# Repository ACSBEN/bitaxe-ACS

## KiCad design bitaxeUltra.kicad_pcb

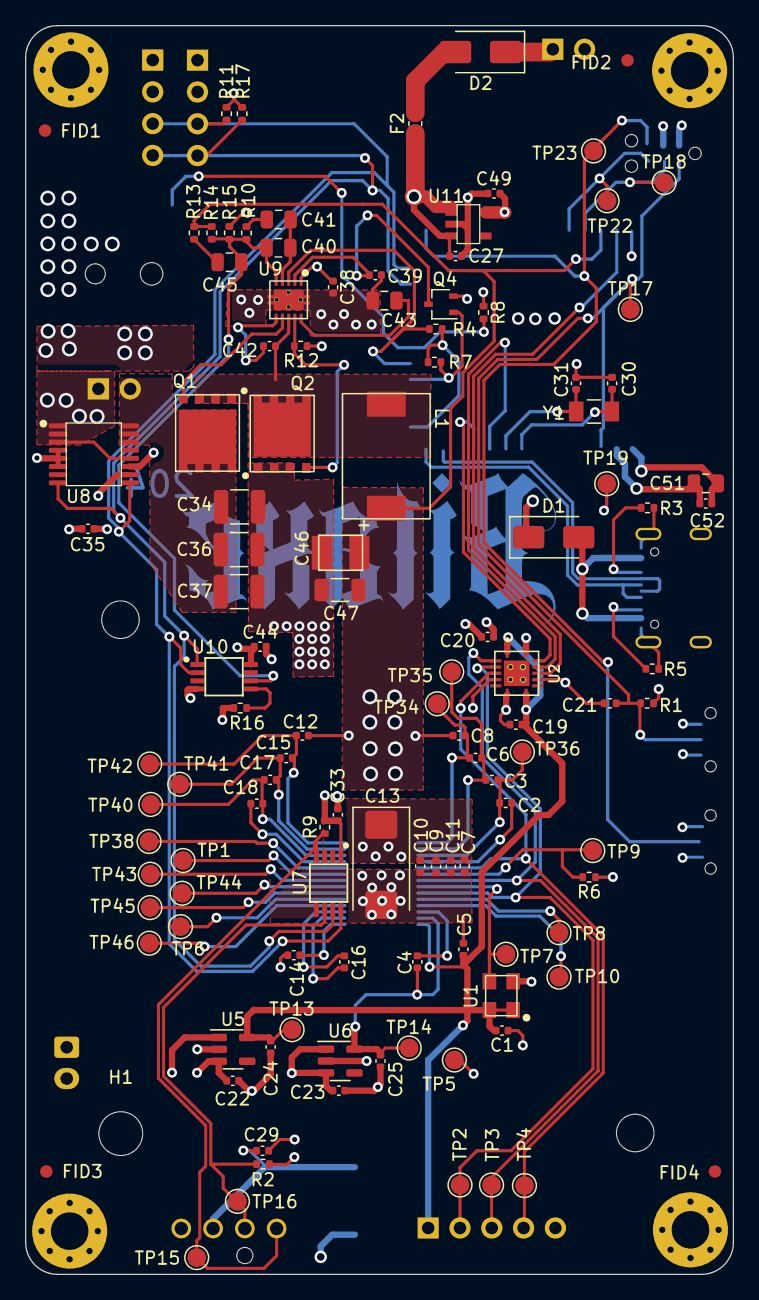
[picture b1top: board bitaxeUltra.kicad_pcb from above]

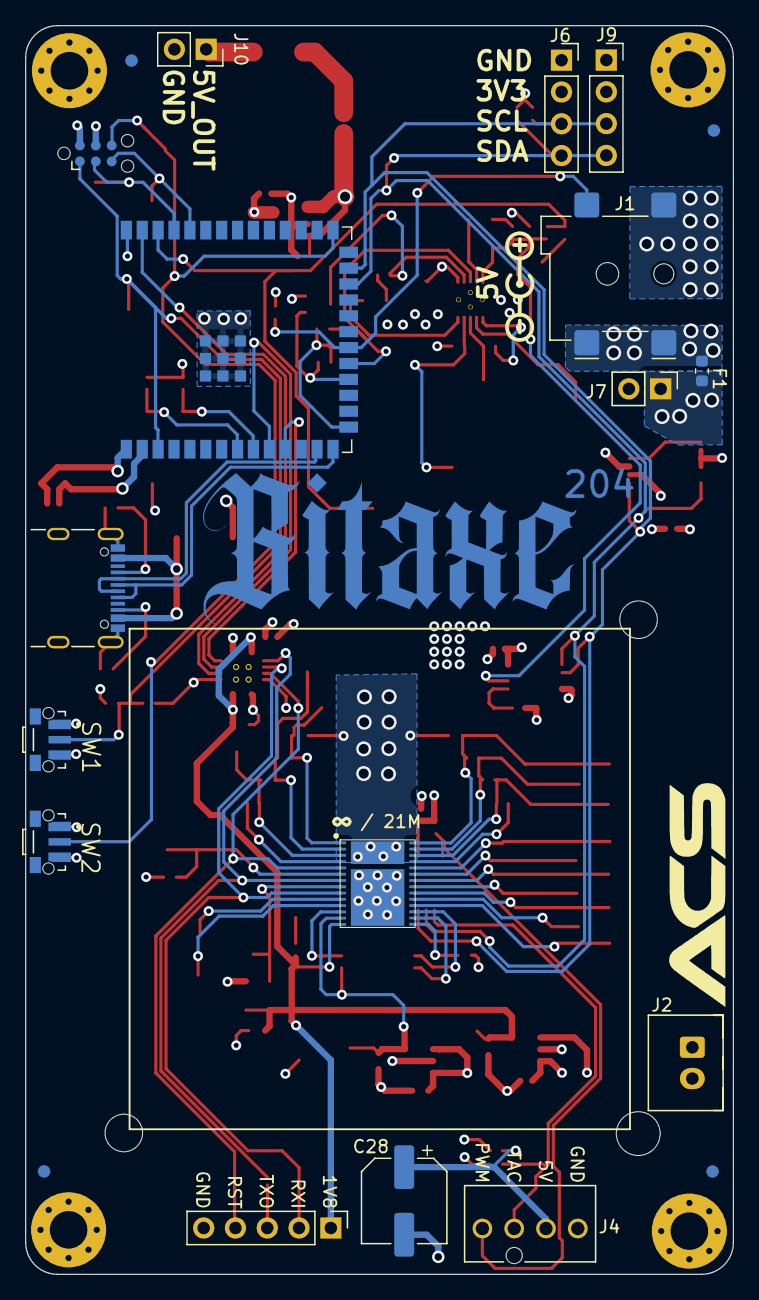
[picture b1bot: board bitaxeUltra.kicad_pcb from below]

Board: 4 copper layers, 56.5 x 99.8 mm, 143 parts (21 on the bottom side), 64 nets.

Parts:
C1, C7, C9, C19, C20, C29, C33, C42, C52: 0.1uF; C_0402_1005Metric
C2, C3, C4, C5, C6, C8, C10, C11, C12, C14, C15, C16, C17, C18, C21, C22, C23, C24, C25, C27, C35, C38, C44, C49: 1uF; C_0402_1005Metric
C13: 330uF; CP_EIA-7343-31_Kemet-D_Pad2.25x2.55mm_HandSolder
C28: 220uF; CP_Elec_6.3x7.7
C30, C31: 6.8pF; C_0402_1005Metric
C34, C36, C37: 47uF; C_1210_3225Metric
C39: 3.3nF; C_0402_1005Metric
C40: 180pF; C_0805_2012Metric
C41: 1.5nF; C_0805_2012Metric
C43, C51: 10uF; C_0805_2012Metric
C45: 470pF; C_0805_2012Metric
C46: 220uF; CAP_2R5TPE220MAFB
C47: 100uF; C_1206_3216Metric
D1, D2: SS310; D_SMA
F1: 5v 5a; Fuse_0603_1608Metric
F2: 5v 1A; Fuse_0603_1608Metric
FID1, FID2, FID3, FID4, FID5, FID6, FID7, FID8: Fiducial; Fiducial_1mm_Mask2mm
H1, H5, H6: MountingHole; MountingHole_3.5mm
H7, H8, H9, H10: MountingHole_Pad; MountingHole_3mm_Pad_Via
J1: 54-00164; BarrelJack_Wuerth_694106106102_2.0x5.5mm
J2: Conn_01x02; JST_XH_B2B-XH-A_1x02_P2.50mm_Vertical
J3: Conn_01x05; PinHeader_1x05_P2.54mm_Vertical
J4: Conn_01x04; 470531000
J5: TC2030-IDC; Tag-Connect_TC2030-IDC-NL_2x03_P1.27mm_Vertical
J6, J9: Conn_01x04; PinSocket_1x04_P2.54mm_Vertical
J7: Conn_01x02; PinHeader_1x02_P2.54mm_Vertical
J8: USB_C_Receptacle_USB2.0; USB_C_Receptacle_GCT_USB4105-xx-A_16P_TopMnt_Horizontal
J10: Conn_01x02; PinSocket_1x02_P2.54mm_Vertical
L1: 150nH; FP1005R1-R15-R
Q1, Q2: CSD17311Q5
Q4: 2N7002K; SOT-323_SC-70
R1, R4, R6, R7, R9: 10k; R_0402_1005Metric
R2: 5.6k; R_0402_1005Metric
R3, R5: 5.1k; R_0402_1005Metric
R8: 1M; R_0402_1005Metric
R10: 3.83k; R_0402_1005Metric
R11, R17: 4.7k; R_0402_1005Metric
R12: 4.12k; R_0402_1005Metric
R13: 1.33k; R_0402_1005Metric
R14: 4.99k; R_0402_1005Metric
R15: 3.32k; R_0402_1005Metric
R16: 80.6k; R_0402_1005Metric
SW1, SW2: GT-TC029B-H025-L1N; SW_TL3340AF160QG
TP1, TP2, TP3, TP4, TP5, TP6, TP7, TP8, TP9, TP10, TP13, TP14, TP15, TP16, TP17, TP18, TP19, TP22, TP23, TP34, TP35, TP36, TP38, TP40, TP41, TP42, TP43, TP44, TP45, TP46: TestPoint; TestPoint_Pad_D1.5mm
U1: 25MHz; O 25,0-JO32-B-1V3-1-T1-LF
U2: TXB0104RGYR; TXB0104
U3: polarity
U5: MCP1824T-1802E; SOT-23-5
U6: MCP1824T-0802E; SOT-23-5
U7: EMC2101; TSSOP-8_3x3mm_P0.65mm
U8: INA260; TSSOP-16_4.4x5mm_P0.65mm
U9: TPS40305
U10: DS4432U+; TSSOP-8_3x3mm_P0.65mm
U11: RT9080-33GJ5
U12: ESP32-S3-WROOM-1
U14: BM1366_mode1; BM1366
Y1: 32.768kHz; SC32S-7PF20PPM

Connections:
/3V3: C20.1, C33.1, C35.1, C44.1, C49.1, C51.1, C52.1, J5.2, J6.2, J9.2, R1.1, R2.2, R4.1, R7.1, R8.1, R9.2, R11.2, R17.2, TP19.1, U2.14 (VCCB), U7.1 (VDD), U8.10 (VS), U10.8 (VCC), U11.5 (VOUT), U12.2 (3V3), U12.15 (GPIO3/TOUCH3/ADC1_CH2*)
/5V: C22.1, C23.1, C27.1, C28.1, C29.1, C34.1, C36.1, C37.1, C38.1, D1.1, F2.1, J2.2, J4.2, J7.2, Q1.5 (D), U5.1 (VIN), U5.3 (EN), U6.1 (VIN), U6.3 (EN), U8.14 (IN-), U8.15 (IN-), U8.16 (IN-), U9.1 (VDD), U11.1 (VIN), U11.3 (EN)
/BM1366/0V8: C4.1, C25.1, TP14.1, U6.5 (VOUT), U14.13 (VDDIO_08_0)
/BM1366/1V8: C1.2, C5.1, C19.1, C24.1, J3.1, TP13.1, U1.1 (EN), U1.4 (VIN), U2.1 (VCCA), U2.8 (OE), U5.5 (VOUT), U14.14 (VDDIO_18_0)
/BM1366/ADDR0: TP8.1, U14.10 (ADDR0)
/BM1366/ADDR1: TP10.1, U14.11 (ADDR1)
/BM1366/BI: R6.2, TP9.1, U14.6 (BI)
/BM1366/BO: TP1.1, U14.23 (BO)
/BM1366/CI: J3.2, TP2.1, U2.3 (A2), U14.9 (CI)
/BM1366/CLKI: TP7.1, U1.3 (OUT), U14.8 (CLKI)
/BM1366/CLKO: TP44.1, U14.21 (CLKO)
/BM1366/CO: TP45.1, U14.20 (CO)
/BM1366/INV_CLKO: TP6.1, U14.19 (INV_CLKO)
/BM1366/NRSTO: TP38.1, U14.24 (NRSTO)
/BM1366/PIN_MODE: TP46.1, U14.18 (PIN_MODE)
/BM1366/RI: TP43.1, U14.22 (RI)
/BM1366/RO: J3.3, TP3.1, U2.2 (A1), U14.7 (RO)
/BM1366/RST_N: J3.4, TP4.1, U2.4 (A3), U14.5 (NRSTI)
/BM1366/VDD1_0: C6.2, C8.1, TP34.1, U14.1 (VDD1_0)
/BM1366/VDD1_1: C12.2, C15.1, TP42.1, U14.28 (VDD1_1)
/BM1366/VDD2_0: C3.2, C6.1, TP35.1, U14.2 (VDD2_0)
/BM1366/VDD2_1: C15.2, C17.1, TP41.1, U14.27 (VDD2_1)
/BM1366/VDD3_0: C2.2, C3.1, TP36.1, U14.3 (VDD3_0)
/BM1366/VDD3_1: C17.2, C18.1, TP40.1, U14.26 (VDD3_1)
/ESP32/5V_OUT: D2.1, J10.1
/ESP32/EN: C21.1, J5.1, R1.2, SW1.2, TP17.1, U12.3 (EN)
/ESP32/IO0: J5.6, SW2.2, TP23.1, U12.27 (GPIO0/BOOT*)
/ESP32/PWR_EN: Q4.1 (G), R7.2, U12.18 (GPIO10/TOUCH10/ADC1_CH9/FSPICS0/FSPIIO4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)
/ESP32/P_RX: J5.5, TP22.1, U12.36 (U0RXD/GPIO44/CLK_OUT2)
/ESP32/P_TX: J5.3, TP18.1, U12.37 (U0TXD/GPIO43/CLK_OUT1)
/ESP32/XIN32: C30.1, U12.8 (GPIO15/U0RTS/ADC2_CH4/XTAL_32K_P), Y1.1
/ESP32/XOUT32: C31.1, U12.9 (GPIO16/U0CTS/ADC2_CH5/XTAL_32K_NH5), Y1.2
/Fan/FAN_PWM: J4.4, R9.1, TP15.1, U7.4 (FAN)
/Fan/FAN_TACH: J4.3, R2.1, TP16.1, U7.6 (ALERT/TACH)
/PLUG_SENSE: J1.3, R8.2, U12.20 (GPIO12/TOUCH12/ADC2_CH1/FSPICLK/FSPIIO6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)
/Power/OUT0: C40.2, C45.2, R10.2, R14.2, R15.1, U9.5 (FB), U10.6 (OUT0)
/Power/PGOOD: R4.2, U9.3 (PGOOD), U12.19 (GPIO11/TOUCH11/ADC2_CH0/FSPID/FSPIIO5/S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)
/Power/SW: C42.2, L1.1, Q1.1, Q1.2, Q1.3 (S), Q2.5 (D), U9.8 (SW)
/Power/VIN: F1.1, J1.1
/Power/VIN_FUSED: F1.2, J7.1, U8.1 (IN+), U8.2 (IN+), U8.3 (IN+), U8.12 (VBUS)
/RST: U2.11 (B3), U12.39 (GPIO1/TOUCH1/ADC1_CH0)
/RX: U2.13 (B1), U12.11 (GPIO18/U1RXD/ADC2_CH7/CLK_OUT3)
/SCL: J6.3, J9.3, R11.1, U7.8 (SMCLK), U8.9 (SCL), U10.2 (SCL), U12.25 (GPIO48/SPICLK_N/SUBSPICLK_N_DIFF)
/SDA: J6.4, J9.4, R17.1, U7.7 (SMDATA), U8.8 (SDA), U10.1 (SDA), U12.24 (GPIO47/SPICLK_P/SUBSPICLK_P_DIFF)
/TX: U2.12 (B2), U12.10 (GPIO17/U1TXD/ADC2_CH6)
/VDD: C7.1, C8.2, C9.1, C10.1, C11.1, C12.1, C13.1, C46.1, C47.1, L1.2, R13.1, R14.1, U12.38 (GPIO2/TOUCH2/ADC1_CH1), U14.29 (VDD)
GND: C1.1, C2.1, C4.2, C5.2, C7.2, C9.2, C10.2, C11.2, C13.2, C14.2, C16.2, C18.2, C19.2, C20.2, C21.2, C22.2, C23.2, C24.2, C25.2, C27.2, C28.2, C29.2, C30.2, C31.2, C33.2, C34.2, C35.2, C36.2, C37.2, C38.2, C39.2, C43.2, C44.2, C46.2, C47.2, C49.2, C51.2, C52.2, H7.1, H8.1, H9.1, H10.1, J1.2, J2.1, J3.5, J4.1, J5.4, J6.1, J8.A1 (GND), J8.A12 (GND), J8.B1 (GND), J8.B12 (GND), J8.S1 (SHIELD), J9.1, J10.2, Q2.1, Q2.2, Q2.3 (S), Q4.2 (S), R3.1, R5.1, R6.1, R12.2, R15.2, R16.2, SW1.1, SW1.3, SW2.1, SW2.3, TP5.1, U1.2 (GND), U2.5 (A4), U2.7 (GND), U2.10 (B4), U2.15 (GND), U2.16 (GND), U2.17 (GND), U2.18 (GND), U2.19 (GND), U5.2 (GND), U6.2 (GND), U7.5 (GND), U8.4 (A1), U8.5 (A0), U8.6 (GND), U8.11 (GND), U9.11 (GND), U10.4 (GND), U11.2 (GND), U12.1 (GND), U12.40 (GND), U12.41 (GND), U14.4 (VSS), U14.12 (PLL_VSS), U14.17 (VSS), U14.25 (VSS), U14.30 (VSS)
unnamed: C41.2, R10.1
unnamed: C45.1, R13.2
unnamed: D1.2, J8.A4 (VBUS), J8.A9 (VBUS), J8.B4 (VBUS), J8.B9 (VBUS)
unnamed: D2.2, F2.2
unnamed: J8.A5 (CC1), R3.2
unnamed: J8.B5 (CC2), R5.2
unnamed: Q1.4 (G), U9.7 (HDRV)
unnamed: Q2.4 (G), R12.1, U9.9 (LDRV)
unnamed: C39.1, Q4.3 (D), U9.2 (EN/SS)
unnamed: C42.1, U9.6 (BOOT)
unnamed: C43.1, U9.10 (BP)
unnamed: C40.1, C41.1, U9.4 (COMP)
unnamed: R16.1, U10.5 (FS0)
unnamed: J8.A7 (D-), J8.B7 (D-), U12.13 (GPIO19/U1RTS/ADC2_CH8/CLK_OUT2/USB_D-)
unnamed: J8.A6 (D+), J8.B6 (D+), U12.14 (GPIO20/U1CTS/ADC2_CH9/CLK_OUT1/USB_D+)
unnamed: C16.1, U14.16 (VDDIO_08_1)
unnamed: C14.1, U14.15 (VDDIO_18_1)

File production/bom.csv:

Designator,Footprint,Quantity,Value,LCSC Part #
"C1, C19, C20, C29, C33, C42, C52, C7, C9",0402,9,0.1uF,
"C10, C11, C12, C14, C15, C16, C17, C18, C2, C21, C22, C23, C24, C25, C27, C3, C35, C38, C4, C44, C49, C5, C6, C8",0402,24,1uF,
C13,CP_EIA-7343-31_Kemet-D_Pad2.25x2.55mm_HandSolder,1,330uF,
C28,CP_Elec_6.3x7.7,1,220uF,
"C30, C31",0402,2,6.8pF,
"C34, C36, C37",1210,3,47uF,
C39,0402,1,3.3nF,
C40,0805,1,180pF,
C41,0805,1,1.5nF,
"C43, C51",0805,2,10uF,
C45,0805,1,470pF,
C46,CAP_2R5TPE220MAFB,1,220uF,
C47,1206,1,100uF,
D2,D_SMA,1,SS310,
F1,0603,1,5v 5a,
F2,0603,1,5v 1A,
J1,BarrelJack_Wuerth_694106106102_2.0x5.5mm,1,54-00164,
J10,PinSocket_1x02_P2.54mm_Vertical,1,Conn_01x02,
J2,JST_XH_B2B-XH-A_1x02_P2.50mm_Vertical,1,Conn_01x02,
J4,470531000,1,Conn_01x04,
J8,USB_C_Receptacle_GCT_USB4105-xx-A_16P_TopMnt_Horizontal,1,USB_C_Receptacle_USB2.0,
L1,FP1005R1-R15-R,1,150nH,
"Q1, Q2",CSD17311Q5,2,CSD17311Q5,
Q4,SOT-323_SC-70,1,2N7002K,
"R1, R4, R6, R7, R9",0402,5,10k,
R10,0402,1,3.83k,
"R11, R17",0402,2,4.7k,
R12,0402,1,4.12k,
R13,0402,1,1.33k,
R14,0402,1,4.99k,
R15,0402,1,3.32k,
R16,0402,1,80.6k,
R2,0402,1,5.6k,
"R3, R5",0402,2,5.1k,
R8,0402,1,1M,
"SW1, SW2",SW_TL3340AF160QG,2,GT-TC029B-H025-L1N,
U1,"O 25,0-JO32-B-1V3-1-T1-LF",1,25MHz,
U10,TSSOP-8_3x3mm_P0.65mm,1,DS4432U+,
U11,RT9080-33GJ5,1,RT9080-33GJ5,
U12,ESP32-S3-WROOM-1,1,ESP32-S3-WROOM-1,
U14,BM1366,1,BM1366_mode1,
U2,TXB0104,1,TXB0104RGYR,
U5,SOT-23-5,1,MCP1824T-1802E,
U6,SOT-23-5,1,MCP1824T-0802E,
U7,TSSOP-8_3x3mm_P0.65mm,1,EMC2101,
U8,TSSOP-16_4.4x5mm_P0.65mm,1,INA260,
U9,TPS40305,1,TPS40305,
Y1,SC32S-7PF20PPM,1,32.768kHz,

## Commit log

2024-11-26 added new i2c connector, power connector, and supporting components
2024-11-26 added 90 degree buttons
2024-11-26 fixing DRC
2024-11-26 added 3rs heatsink mounting hole
2024-11-26 added sda and scl puulups
2024-11-26 small tweak
2024-11-26 added gerbers
2024-11-26 added position file
2024-11-26 more BOMS
